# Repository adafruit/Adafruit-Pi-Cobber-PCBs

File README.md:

## Adafruit Pi Cobber PCBs
&nbsp; <br />
&nbsp; <br />

The Raspberry Pi B+/Pi 2/ Pi 3 has landed on the Maker World like a 20 or 40-GPIO pinned, quad-USB ported, credit card sized bomb of DIY joy. And while you can use most of our great Model B accessories by hooking up our downgrade cable, its probably a good time to upgrade your set up and accessorize using all of the Model B+'s / Pi 2's / Pi 3's 40 pins.

That's why we now carry the Adafruit Assembled Pi Cobbler Plus - Breakout and Cable for Raspberry Pi A+, B+, Pi 2 and Pi 3. It's an add on prototyping Pi Cobbler from Adafruit specifically designed for the B+ and Pi 2 that you can break out all those tasty power, GPIO, I2C and SPI pins from the 40-pin header onto a solderless breadboard. This will make "cobbling together" prototypes with the Pi super easy.

Designed for use with Raspberry Pi Model A+/B+/Pi 2/Pi 3 only! No soldering required!

This Cobbler is in a compact shape, which is the least bulky way to wire up. The cable plugs between the Pi A+/B+/Pi 2/Pi 3 computer and the Cobbler breakout. The Cobbler can plug into any solderless breadboard (or even a prototyping board like the PermaProto). The Cobbler PCB has all the pins labeled nicely so you can go forth and build circuits without keeping a pin-out printout at your desk. We think this will make it more fun to expand the Pi and build custom circuitry with it.

For more details, check out all the product pages at
- https://www.adafruit.com/products/914
- https://www.adafruit.com/products/1105
- https://www.adafruit.com/products/1754
- https://www.adafruit.com/products/1989
- https://www.adafruit.com/products/2028
- https://www.adafruit.com/products/2029

PCB files for the Adafruit Pi Cobber and T-Cobbler. Cobbler and T-Cobbler are registered trademarks of Adafruit. The format is EagleCAD schematic and board layout

### License

Adafruit invests time and resources providing this open source design, please support Adafruit and open-source hardware by purchasing products from [Adafruit](https://www.adafruit.com)!

All text above must be included in any redistribution

Designed by Limor Fried/Ladyada for Adafruit Industries.
Creative Commons Attribution/Share-Alike, all text above must be included in any redistribution. 
See license.txt for additional information.

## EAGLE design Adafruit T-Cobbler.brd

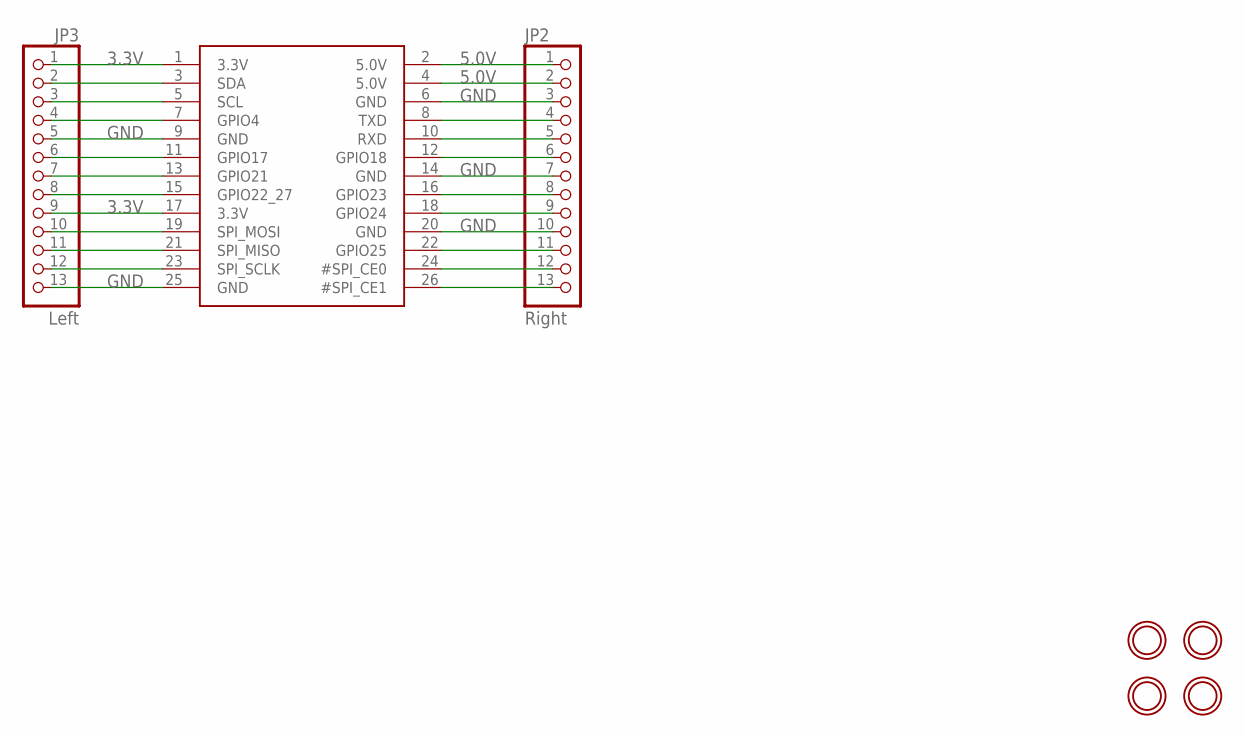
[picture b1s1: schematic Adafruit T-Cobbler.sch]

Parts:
JP1: PI; RASBERRYPI_IDC
JP2: Right; 1X13_ROUND_70
JP3: Left; 1X13_ROUND_70
U$2, U$3, U$4, U$5: MOUNTINGHOLE2.5; MOUNTINGHOLE_2.5_PLATED

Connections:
3.3V: JP1.1 (3.3V), JP1.17 (3.3V), JP3.1, JP3.9
5.0V: JP1.2 (5.0V), JP1.4 (5.0V), JP2.1, JP2.2
GND: JP1.6 (GND), JP1.9 (GND), JP1.14 (GND), JP1.20 (GND), JP1.25 (GND), JP2.3, JP2.7, JP2.10, JP3.5, JP3.13
unnamed: JP1.3 (SDA), JP3.2
unnamed: JP1.5 (SCL), JP3.3
unnamed: JP1.7 (GPIO4), JP3.4
unnamed: JP1.11 (GPIO17), JP3.6
unnamed: JP1.13 (GPIO21), JP3.7
unnamed: JP1.15 (GPIO22_27), JP3.8
unnamed: JP1.19 (SPI_MOSI), JP3.10
unnamed: JP1.21 (SPI_MISO), JP3.11
unnamed: JP1.23 (SPI_SCLK), JP3.12
unnamed: JP1.8 (TXD), JP2.4
unnamed: JP1.10 (RXD), JP2.5
unnamed: JP1.12 (GPIO18), JP2.6
unnamed: JP1.16 (GPIO23), JP2.8
unnamed: JP1.18 (GPIO24), JP2.9
unnamed: JP1.22 (GPIO25), JP2.11
unnamed: JP1.24 (#SPI_CE0), JP2.12
unnamed: JP1.26 (#SPI_CE1), JP2.13

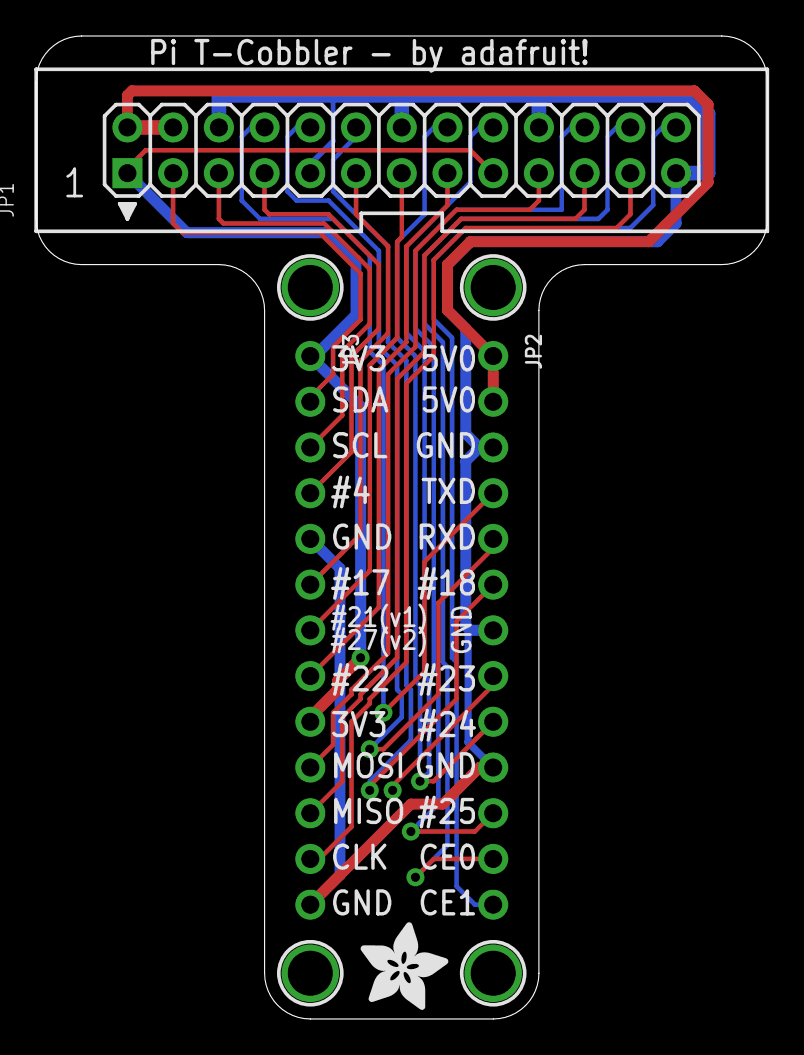
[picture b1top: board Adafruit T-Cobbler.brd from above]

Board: 2 copper layers, 40.6 x 54.6 mm, 8 parts (0 on the bottom side), 20 nets.

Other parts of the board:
U$7: ADAFRUIT_5MM

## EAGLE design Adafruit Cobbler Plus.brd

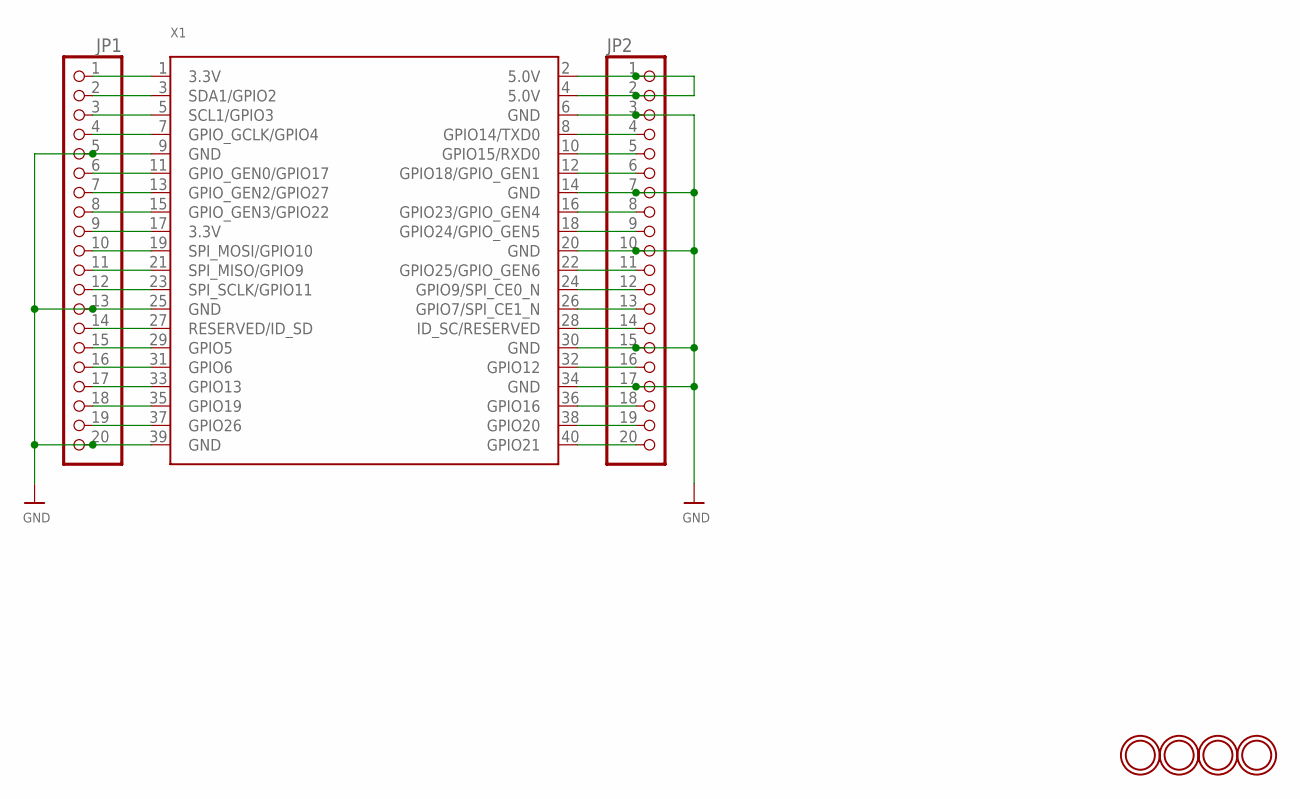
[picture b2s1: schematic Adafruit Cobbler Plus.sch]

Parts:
JP1, JP2: HEADER-1X20ROUND; 1X20_ROUND
U$1, U$2, U$3, U$4: MOUNTINGHOLE2.5_THICK; MOUNTINGHOLE_2.5_PLATED_THICK
X1: RASPBERRYPI_B+_IDC

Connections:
GND: JP1.5, JP1.13, JP1.20, JP2.3, JP2.7, JP2.10, JP2.15, JP2.17, X1.6 (GND), X1.9 (GND), X1.14 (GND), X1.20 (GND), X1.25 (GND), X1.30 (GND), X1.34 (GND), X1.39 (GND)
unnamed: JP2.1, JP2.2, X1.2 (5.0V), X1.4 (5.0V)
unnamed: JP2.4, X1.8 (GPIO14/TXD0)
unnamed: JP2.5, X1.10 (GPIO15/RXD0)
unnamed: JP2.6, X1.12 (GPIO18/GPIO_GEN1)
unnamed: JP2.8, X1.16 (GPIO23/GPIO_GEN4)
unnamed: JP2.9, X1.18 (GPIO24/GPIO_GEN5)
unnamed: JP2.11, X1.22 (GPIO25/GPIO_GEN6)
unnamed: JP2.12, X1.24 (GPIO9/SPI_CE0_N)
unnamed: JP2.13, X1.26 (GPIO7/SPI_CE1_N)
unnamed: JP2.14, X1.28 (ID_SC/RESERVED)
unnamed: JP2.16, X1.32 (GPIO12)
unnamed: JP2.18, X1.36 (GPIO16)
unnamed: JP2.19, X1.38 (GPIO20)
unnamed: JP2.20, X1.40 (GPIO21)
unnamed: JP1.1, X1.1 (3.3V)
unnamed: JP1.2, X1.3 (SDA1/GPIO2)
unnamed: JP1.3, X1.5 (SCL1/GPIO3)
unnamed: JP1.4, X1.7 (GPIO_GCLK/GPIO4)
unnamed: JP1.6, X1.11 (GPIO_GEN0/GPIO17)
unnamed: JP1.7, X1.13 (GPIO_GEN2/GPIO27)
unnamed: JP1.8, X1.15 (GPIO_GEN3/GPIO22)
unnamed: JP1.9, X1.17 (3.3V)
unnamed: JP1.10, X1.19 (SPI_MOSI/GPIO10)
unnamed: JP1.11, X1.21 (SPI_MISO/GPIO9)
unnamed: JP1.12, X1.23 (SPI_SCLK/GPIO11)
unnamed: JP1.14, X1.27 (RESERVED/ID_SD)
unnamed: JP1.15, X1.29 (GPIO5)
unnamed: JP1.16, X1.31 (GPIO6)
unnamed: JP1.17, X1.33 (GPIO13)
unnamed: JP1.18, X1.35 (GPIO19)
unnamed: JP1.19, X1.37 (GPIO26)

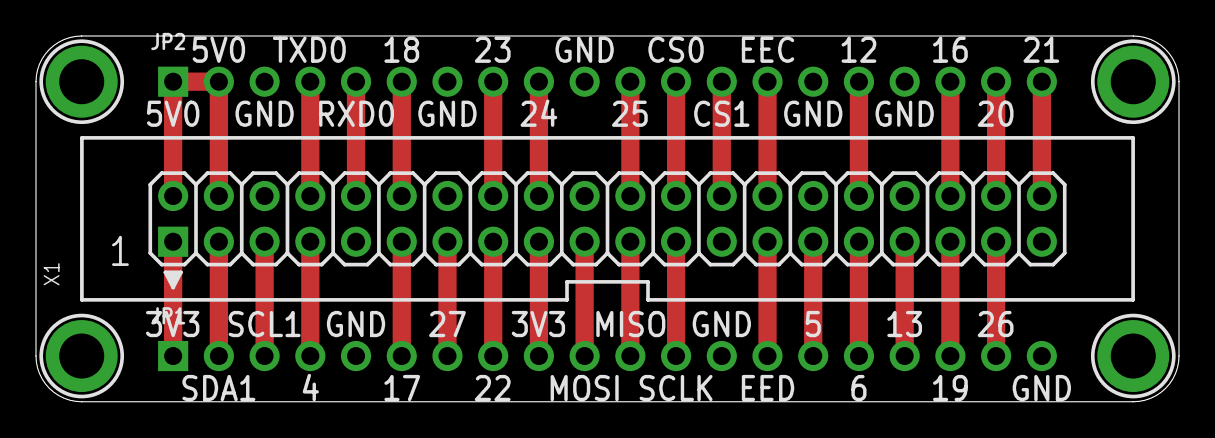
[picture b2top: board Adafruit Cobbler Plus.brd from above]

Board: 2 copper layers, 63.5 x 20.3 mm, 7 parts (0 on the bottom side), 32 nets.

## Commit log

2016-07-17 cobbly

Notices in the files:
parts and their libraries:
microbuilder: This work is placed in the public domain, and may be freely used for commercial and non-commercial work with the following conditions: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
